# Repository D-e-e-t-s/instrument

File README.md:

# MIDI keyboard

This keyboard plays the main notes to the theme song of Howl's Moving Castle using 7 capactive keys. It also includes 3 buttons, 2 sliders, and a waveshare. On the front is a couple details from the movie like calcifer, the dog, and the name of the movie. Then on the back there is howl and sophie. 

It is a PCB with capacitive keys that play notes to a particular song in short. 

# The Why

I made this project because basically for all of my projects on half-life I like putting things about me into these projects and one of my favorite movies of all time has to be Howl's moving castle and I absolutely love the theme song with a passion and what better way to show my love for the movie than create a keyboard that can play the theme song? 

# The process 

I started working on the schematic and used waveshare for my microcontroller and added the remaining parts I included sliders, switches, and LED here is how the schematic looks like after wiring everything: 

Then I worked on my PCB, rearranged the components, and created my edge cuts layer around it. I decided to make my capactive keys like 4 in the top and 3 below it and pretty big too, and then I routed it which took me two hours because it was so difficult heres how it turned out:

Heres how my edge cuts layer looks like:

Heres how the routing looks like:

Then I added designs to my PCB based off of howls moving castle:

Heres how the 3d version looks like: 

After I added images to the back of the PCB too and checked how it looked like in the 3d viewer & added 3d components:

Heres all the 3d components I added:

Then I started looking for my materials!

| Item | Qty | Supplier | Cost/item | Total Cost | Link |
| --- | :---: | --- | ---: | ---: | --- |
| SK6812MINI-E | 1 | AliExpress | $5.19 | $5.19 | [AliExpress](https://aliexpress.us) |
| Waveshare ESP32-S3-Zero | 1 | AliExpress | $3.41 | $3.41 | [AliExpress](https://aliexpress.us) |
| PCB | 1 | JLCPCB | $2.00 | $2.00 | [JLCPCB](https://jlcpcb.com) |
| PTA1543 | 2 | DigiKey | $1.58 | $3.16 | [DigiKey](https://digikey.com) |
| Kailh Choc V2 Silent Low-Profile Switches | 3 | Keebio | $0.70 | $2.10 | [Keebio](https://keeb.io) |
| **Estimated total shipping** | | | | **$7.09** | |
| **Total** | | | | **$22.95** | |

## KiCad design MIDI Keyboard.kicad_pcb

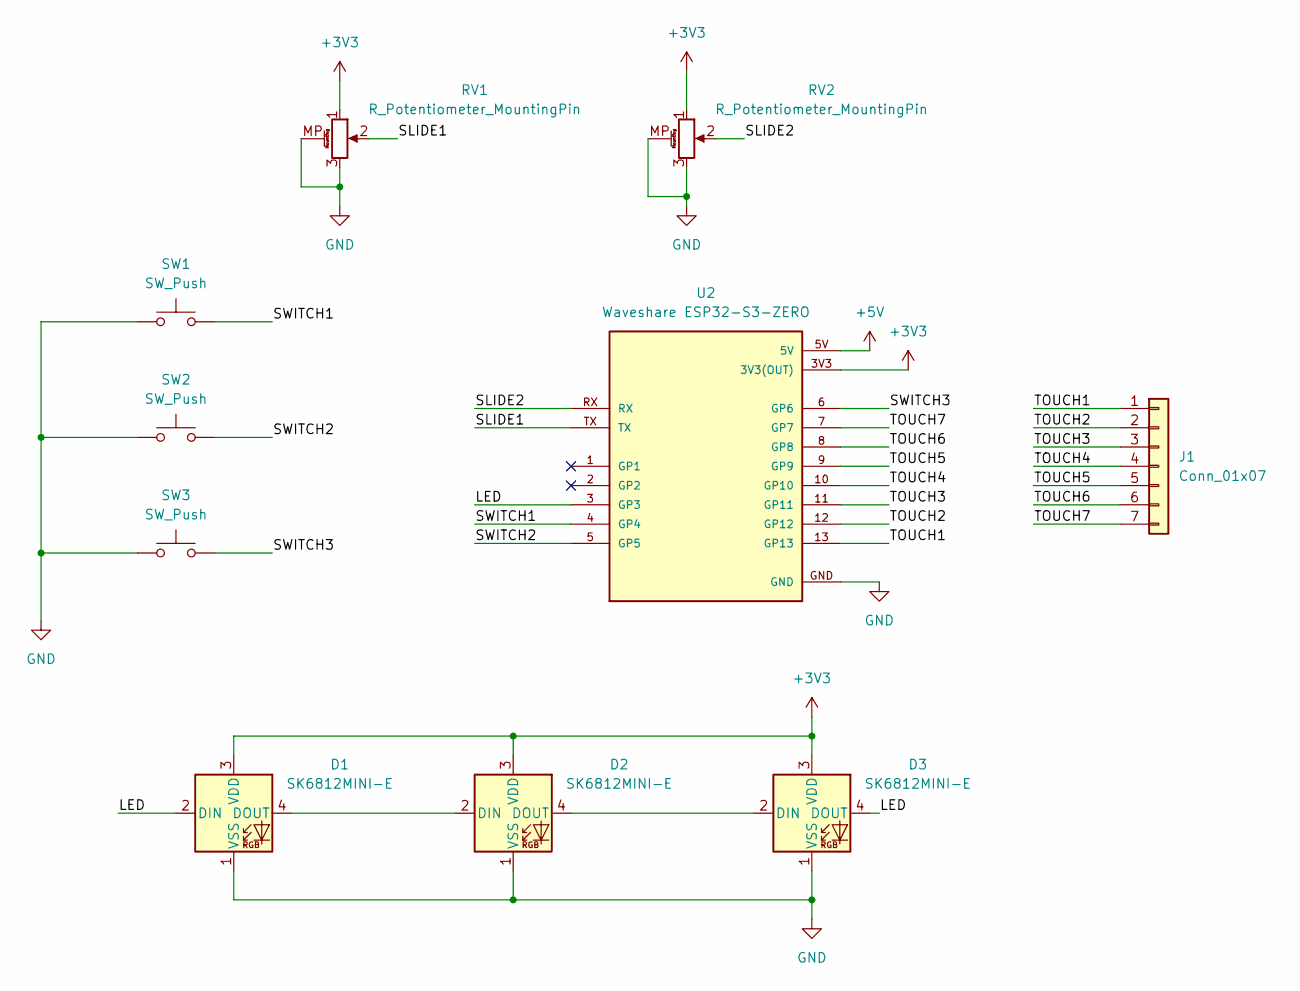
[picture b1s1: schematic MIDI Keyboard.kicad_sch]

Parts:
D1, D2, D3: SK6812MINI-E; LED_SK6812MINI-E_3.2x2.8mm_P1.5mm_ReverseMount
J1: Conn_01x07; Untitled
RV1, RV2: R_Potentiometer_MountingPin; Potentiometer_Bourns_PTA1543_Single_Slide
SW1, SW2, SW3: SW_Push; Kailh Choc Low-Profile Switches
U2: Waveshare ESP32-S3-ZERO; Waveshare ESP32-S3-Zero; PARTREV NA

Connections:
+3V3: D1.3 (VDD), D2.3 (VDD), D3.3 (VDD), RV1.1, RV2.1, U2.3V3 (3V3(OUT))
+5V: U2.5V
/LED: D1.2 (DIN), D3.4 (DOUT), U2.3 (GP3)
/SLIDE1: RV1.2, U2.TX
/SLIDE2: RV2.2, U2.RX
/SWITCH1: SW1.2, U2.4 (GP4)
/SWITCH2: SW2.2, U2.5 (GP5)
/SWITCH3: SW3.2, U2.6 (GP6)
/TOUCH1: J1.1, U2.13 (GP13)
/TOUCH2: J1.2, U2.12 (GP12)
/TOUCH3: J1.3, U2.11 (GP11)
/TOUCH4: J1.4, U2.10 (GP10)
/TOUCH5: J1.5, U2.9 (GP9)
/TOUCH6: J1.6, U2.8 (GP8)
/TOUCH7: J1.7, U2.7 (GP7)
GND: D1.1 (VSS), D2.1 (VSS), D3.1 (VSS), RV1.3, RV1.MP (MountPin), RV2.3, RV2.MP (MountPin), SW1.1, SW2.1, SW3.1, U2.GND
unnamed: D1.4 (DOUT), D2.2 (DIN)
unnamed: D2.4 (DOUT), D3.2 (DIN)

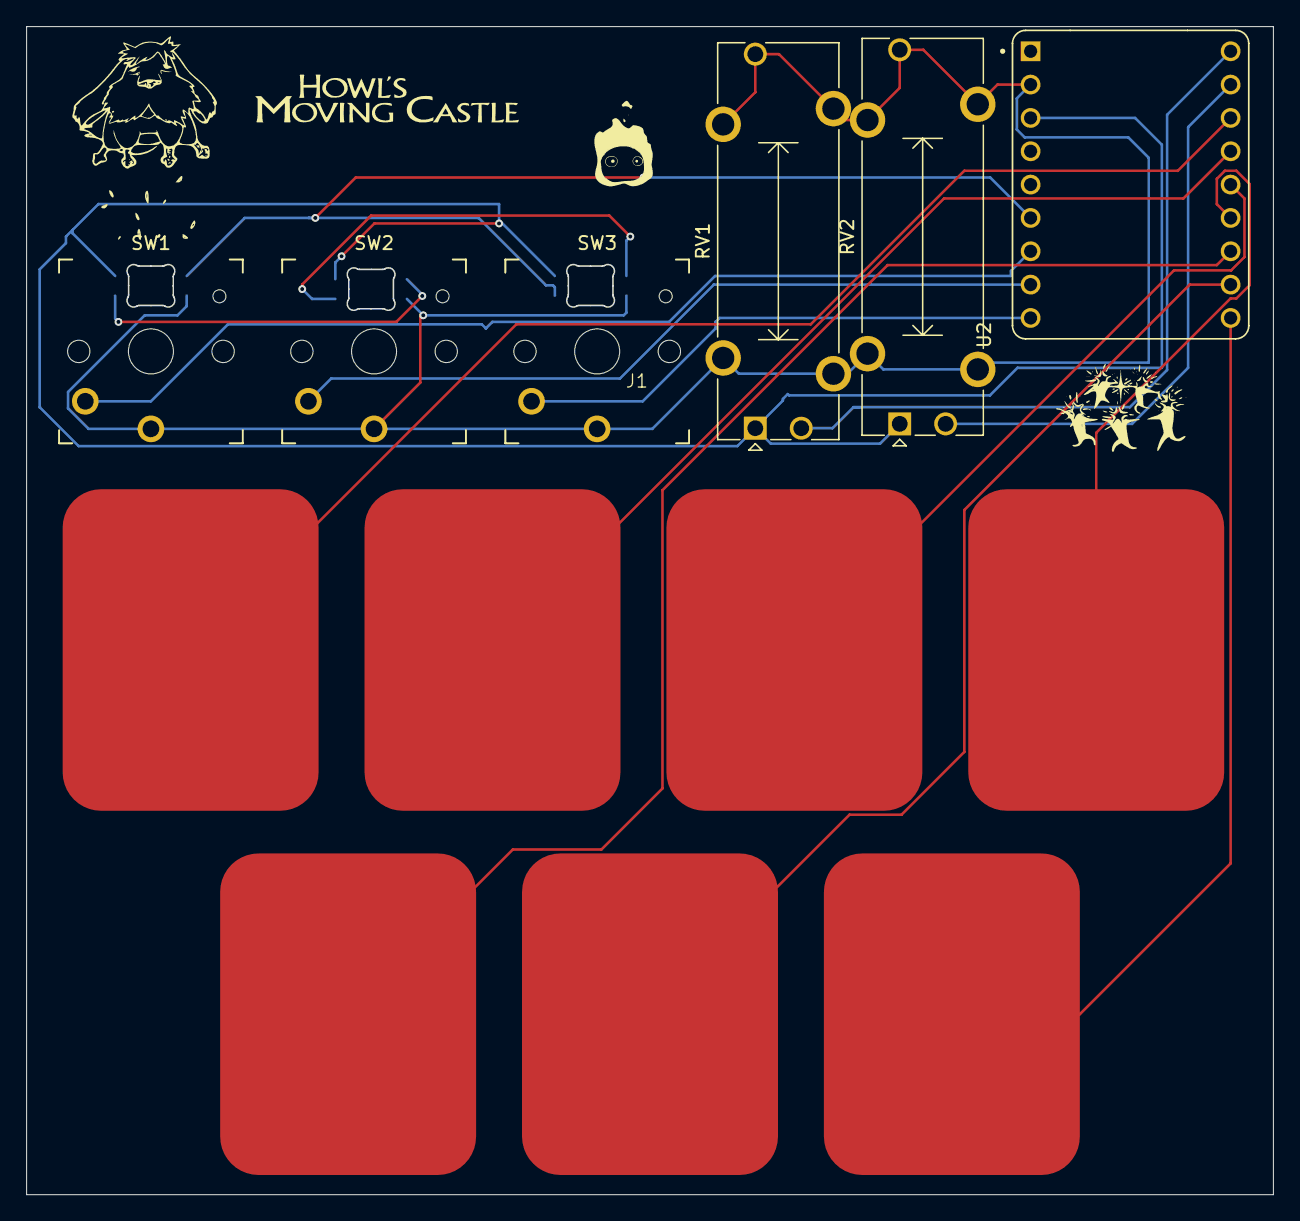
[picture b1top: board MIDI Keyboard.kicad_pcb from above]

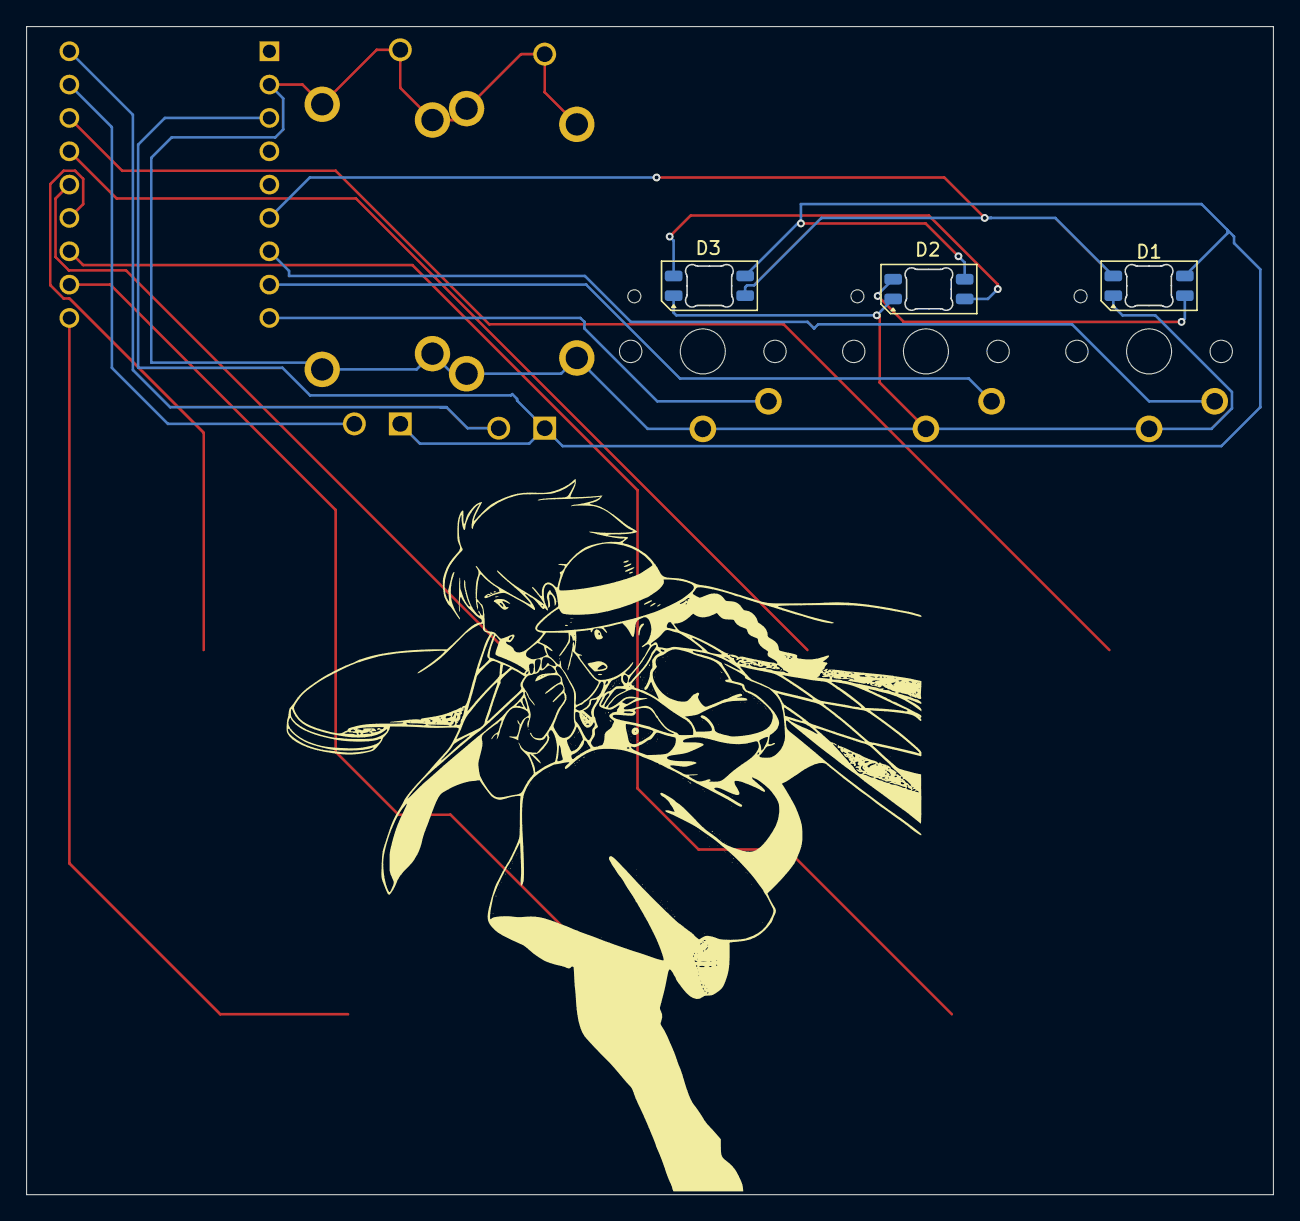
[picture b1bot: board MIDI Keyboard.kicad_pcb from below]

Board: 2 copper layers, 95.0 x 89.0 mm, 10 parts (3 on the bottom side), 17 nets.

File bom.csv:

Designator,Footprint,Quantity,Value,LCSC Part #,QTY,Price,Link
"D1, D2, D3",LED_SK6812MINI-E_3.2x2.8mm_P1.5mm_ReverseMount,3,SK6812MINI-E,,1,$5.19 ,https://www.aliexpress.us/item/3256807390258902.html?src=goo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
J1,Untitled,1,Conn_01x07,,1,$2.00 ,https://cart.jlcpcb.com/shopcart/cart/?_t=1792870921277&spm=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
"RV1, RV2",Potentiometer_Bourns_PTA1543_Single_Slide,2,R_Potentiometer_MountingPin,,2,$1.58 ,https://www.digikey.com/en/products/detail/bourns-inc/PTA154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
"SW1, SW2, SW3",Kailh Choc Low-Profile Switches,3,SW_Push,,3,$0.70 ,https://keeb.io/products/kailh-choc-v2-silent-low-profile-sw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
U2,Waveshare ESP32-S3-Zero,1,Waveshare ESP32-S3-ZERO,,1,$3.41 ,https://www.aliexpress.us/item/3256812546916539.html?spm=a2g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
,,,Shipping,,,$7.09 ,
,,,Total,,,$22.95 ,


**This one is just the file I uploaded go to the BOM.csv for the actual better table
